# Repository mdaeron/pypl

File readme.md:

# Python Prep Line (PyPL)

An open source / open hardware automation system. Originally designed for processing geochemichal samples in our stable isotope lab, but the system is flexible enough to fit many other needs.

## Core design

* Microcontrollers are not encumbered by a full OS, yet can reliably run simple tasks with low latency (μs to ms).
* PyPL uses a *pyboard*, a microcontroller running MicroPython (a full-featured Python implementation running on “bare metal”) to communicate asynchronously with sensors
(T, P, H), and actuators (stepper motors, relays, valves, heating elements...).
* The board is also connected to a full-fledged computer (e.g., a Raspberry Pi or something more expensive) which provides a GUI and logs/syncs/backups data.
* PyPL mostly uses cheap (2–20 €) breakout boards for electronic components, making most repairs plug-and-play. These boards are cheap enough that you can have spare ones, further simplifying hardware maintenance.
* All code, whether on the pyboard or on the computer, is regular Python, promoting painless
development, rapid iteration, and future-proof code.

## Documentation

Full documentation (work in progress) is [here](https://mdaeron.github.io/pypl/).

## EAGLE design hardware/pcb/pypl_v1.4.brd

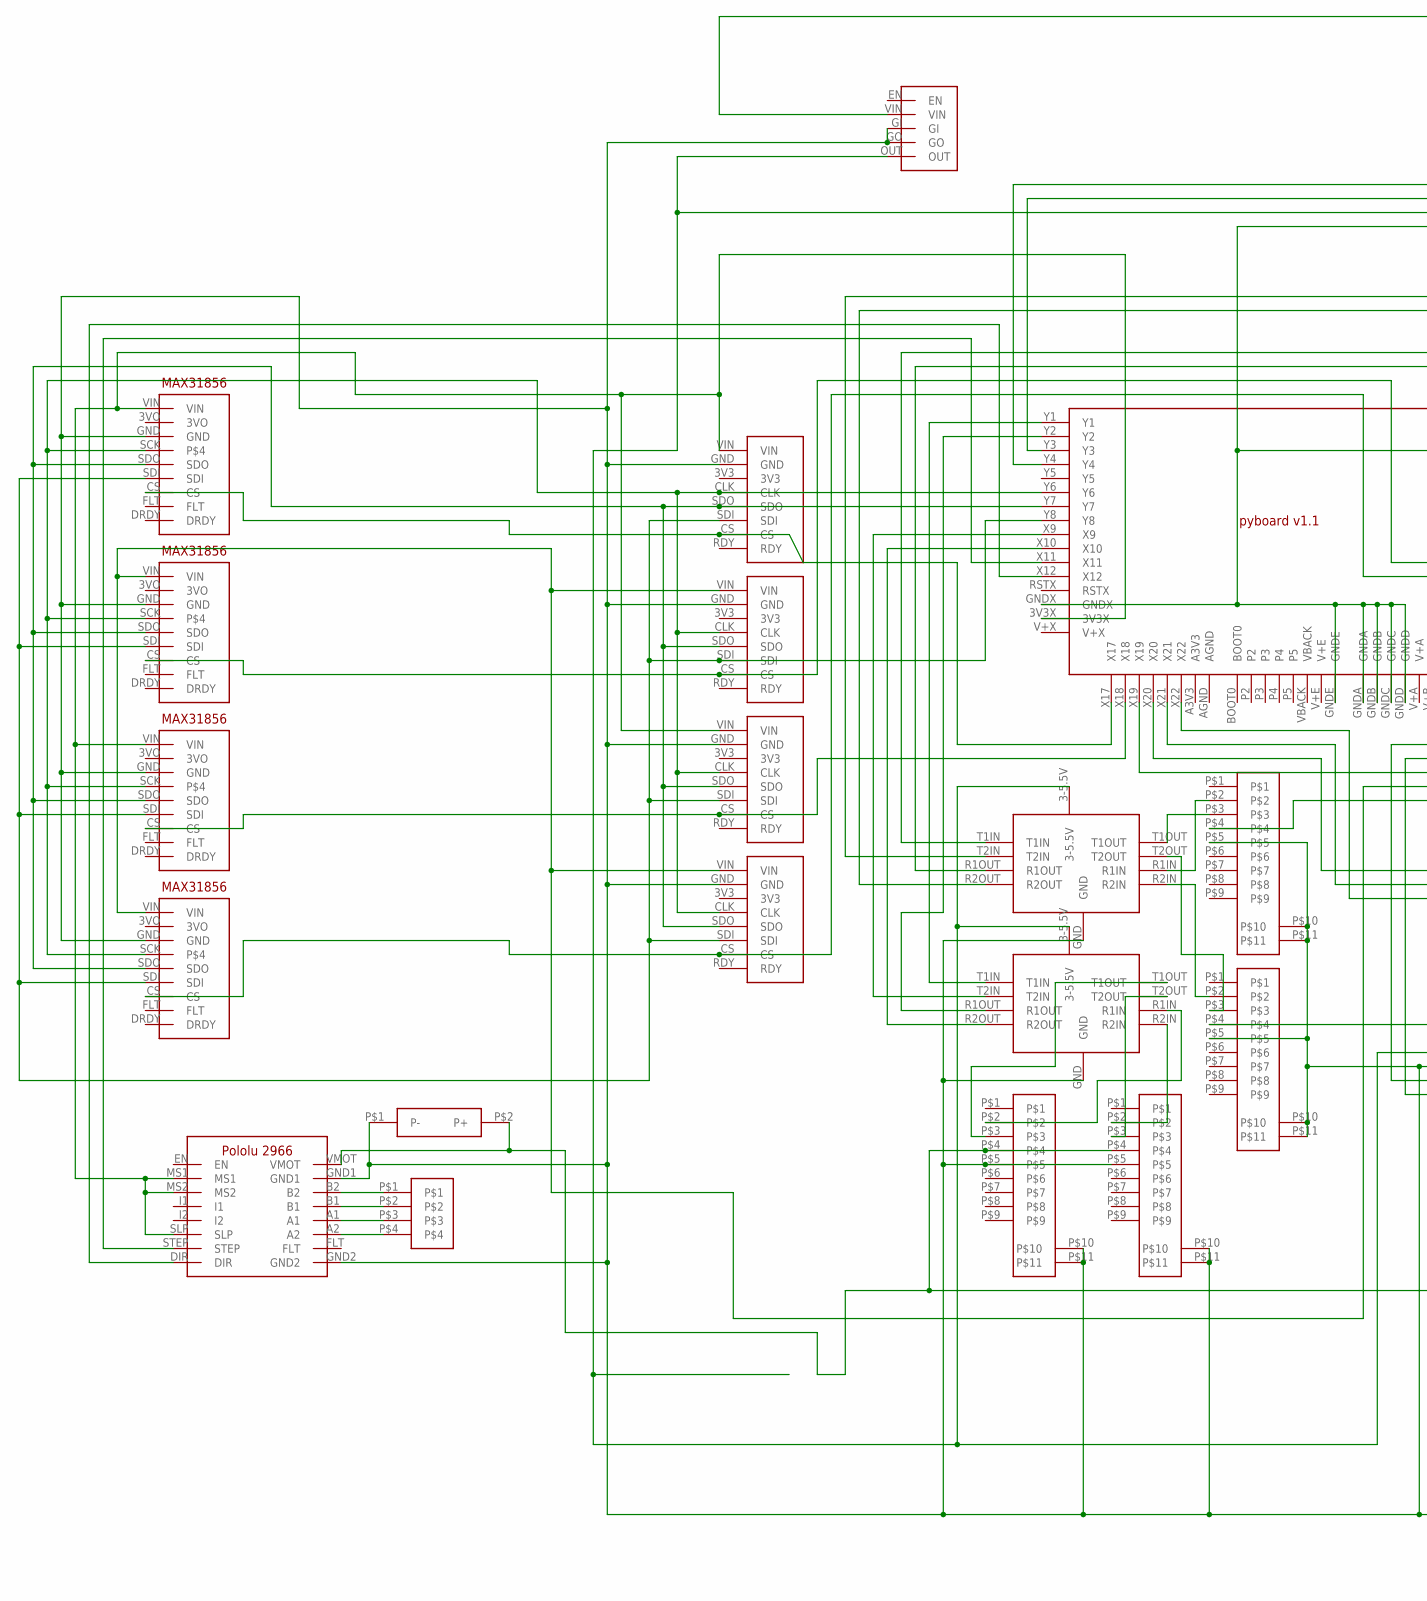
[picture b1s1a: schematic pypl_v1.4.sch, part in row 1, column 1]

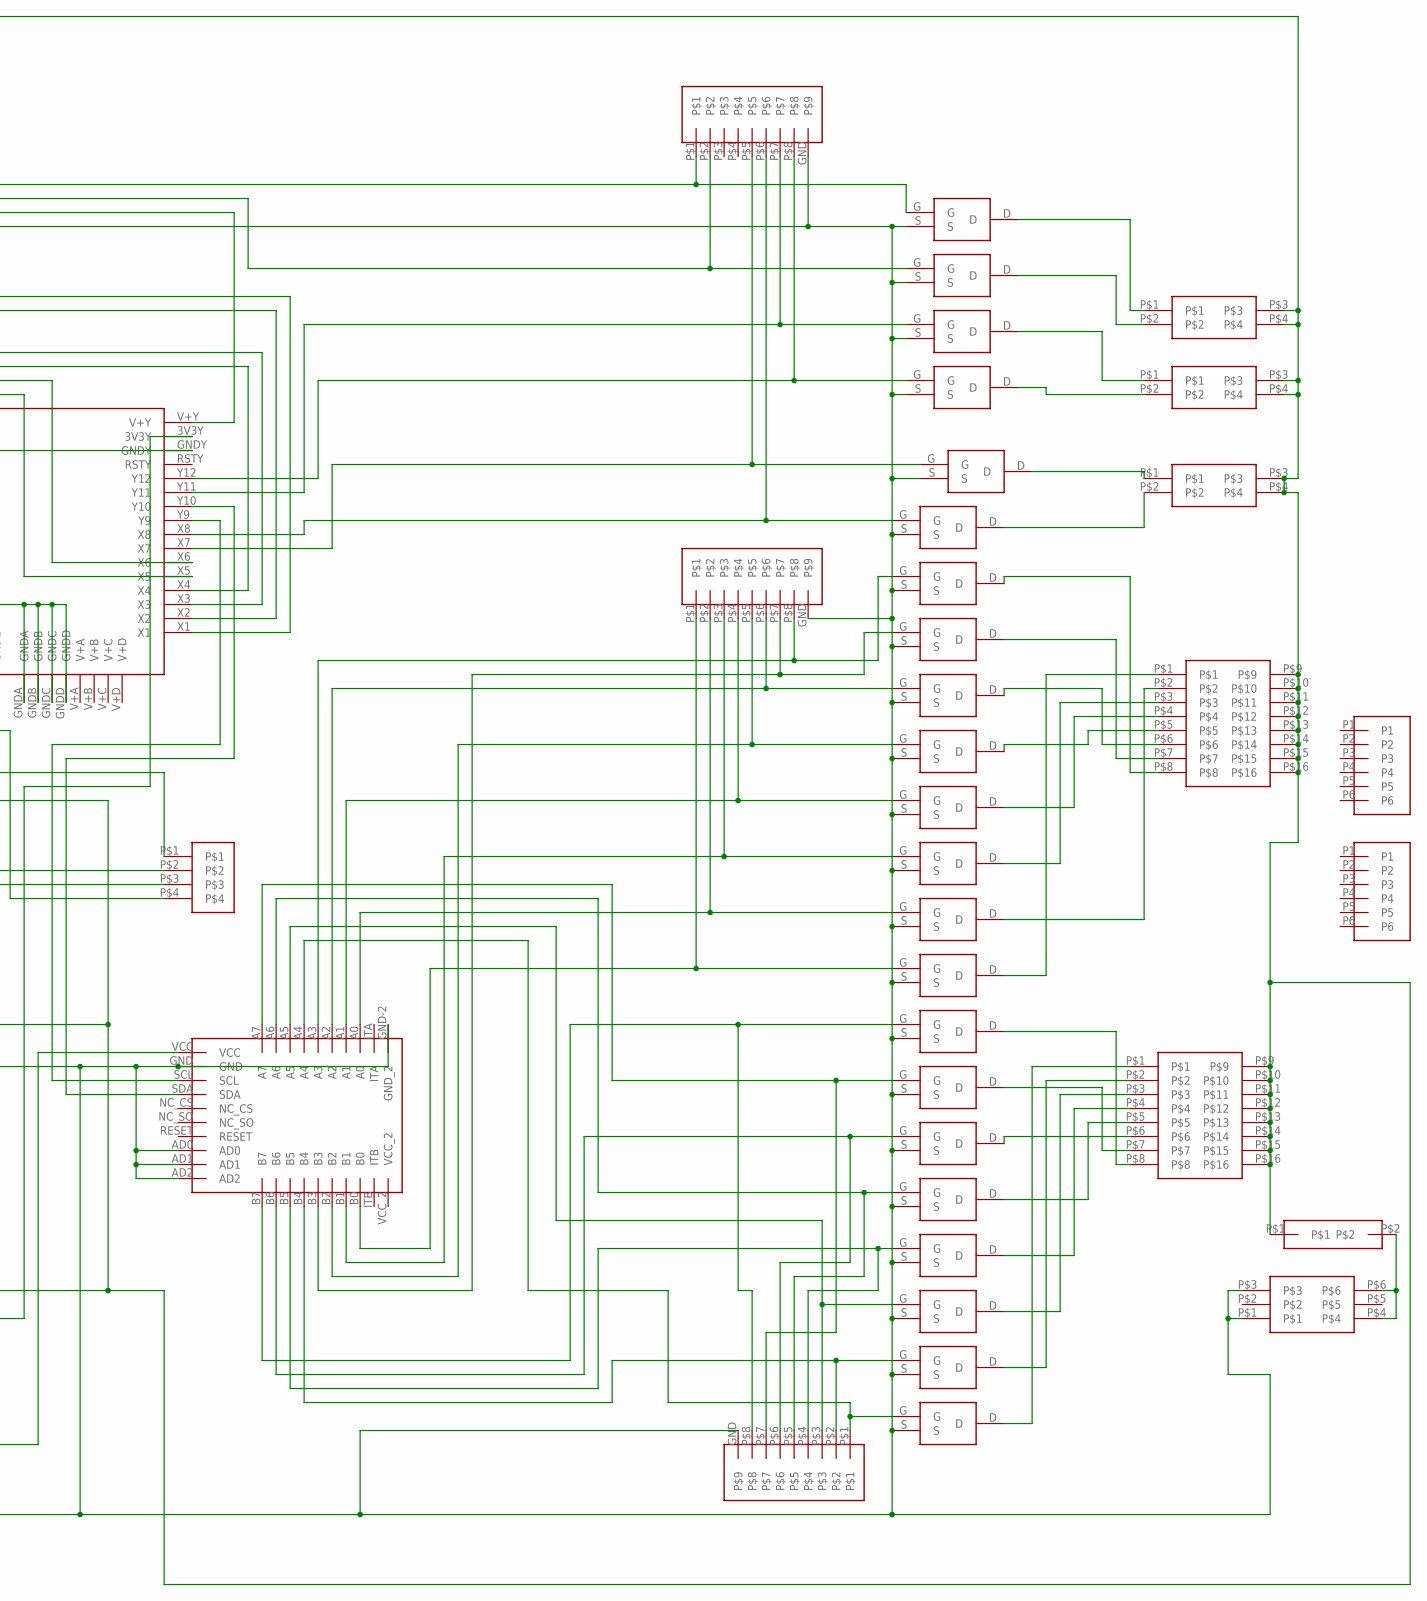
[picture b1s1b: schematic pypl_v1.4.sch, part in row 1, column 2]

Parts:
U$1, U$23, U$25, U$26: MAX31865
U$2, U$3, U$4, U$5, U$6, U$7, U$8, U$9, U$11, U$12, U$13, U$14, U$15, U$16, U$17, U$18, U$33, U$34, U$42, U$43, U$44, U$45: IRLB8721PBF
U$10: MCP23017
U$19, U$20, U$21, U$22: DSUB-9
U$24: PYBOARD_V1.1
U$27, U$28: BORNIER_DUPLEX_X16
U$29: CAP-GOTRONIC-04936
U$30, U$46: BORNIER_1X4_2.54
U$31: PORTE-FUSIBLE
U$32: MP6500-2966
U$35, U$40, U$41: BORNIER_DUPLEX_X4
U$36, U$37: BOB-1189; BOB-11189
U$38: MOLEX_MINIFT_JR_ANGLED_X6
U$39: D24V50F5D24V50F5; D24V50F5
U$47, U$48, U$49: RESISTOR_BANK_BUSSED_X8
U$50, U$51, U$52, U$53: MAX31856
U$54, U$55: PINH06

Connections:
GND: U$1.GND, U$2.S, U$3.S, U$4.S, U$5.S, U$6.S, U$7.S, U$8.S, U$9.S, U$10.AD0, U$10.AD1, U$10.AD2, U$10.GND, U$10.GND-2 (GND_2), U$11.S, U$12.S, U$13.S, U$14.S, U$15.S, U$16.S, U$17.S, U$18.S, U$19.P$5, U$19.P$10, U$19.P$11, U$20.P$5, U$20.P$10, U$20.P$11, U$21.P$5, U$21.P$10, U$21.P$11, U$22.P$5, U$22.P$10, U$22.P$11, U$23.GND, U$24.GNDA, U$24.GNDB, U$24.GNDC, U$24.GNDD, U$24.GNDE, U$24.GNDX, U$24.GNDY, U$25.GND, U$26.GND, U$29.P$1 (P-), U$32.GND1, U$32.GND2, U$33.S, U$34.S, U$36.GND, U$37.GND, U$38.P$1, U$38.P$3, U$39.GI, U$39.GO, U$42.S, U$43.S, U$44.S, U$45.S, U$47.GND, U$48.GND, U$49.GND, U$50.GND, U$51.GND, U$52.GND, U$53.GND
unnamed: U$24.X12, U$32.DIR
unnamed: U$10.SDA, U$24.Y10
unnamed: U$10.SCL, U$24.Y9
unnamed: U$24.X4, U$36.R1OUT
unnamed: U$24.X3, U$36.T1IN
unnamed: U$24.X2, U$36.R2OUT
unnamed: U$24.X1, U$36.T2IN
unnamed: U$24.Y1, U$37.T1IN
unnamed: U$24.Y2, U$37.R1OUT
unnamed: U$24.X10, U$37.R2OUT
unnamed: U$24.X9, U$37.T2IN
unnamed: U$1.CLK, U$23.CLK, U$24.Y6, U$25.CLK, U$26.CLK, U$50.SCK, U$51.SCK, U$52.SCK, U$53.SCK
unnamed: U$1.SDO, U$23.SDO, U$24.Y7, U$25.SDO, U$26.SDO, U$50.SDO, U$51.SDO, U$52.SDO, U$53.SDO
unnamed: U$1.SDI, U$23.SDI, U$24.Y8, U$25.SDI, U$26.SDI, U$50.SDI, U$51.SDI, U$52.SDI, U$53.SDI
unnamed: U$10.A7, U$15.G, U$47.P$7
unnamed: U$4.G, U$10.B2, U$48.P$5
unnamed: U$7.G, U$10.A3, U$48.P$8
unnamed: U$6.G, U$10.B3, U$48.P$7
unnamed: U$5.G, U$10.A2, U$48.P$6
unnamed: U$3.G, U$10.A1, U$48.P$4
unnamed: U$2.G, U$10.B1, U$48.P$3
unnamed: U$8.G, U$10.A0, U$48.P$2
unnamed: U$9.G, U$10.B0, U$48.P$1
unnamed: U$10.B4, U$17.G, U$47.P$2
unnamed: U$10.B5, U$12.G, U$47.P$4
unnamed: U$10.B6, U$14.G, U$47.P$6
unnamed: U$10.B7, U$16.G, U$47.P$8
unnamed: U$10.A6, U$13.G, U$47.P$5
unnamed: U$7.D, U$28.P$8
unnamed: U$6.D, U$28.P$7
unnamed: U$5.D, U$28.P$6
unnamed: U$30.P$1, U$32.B2
unnamed: U$16.D, U$27.P$8
unnamed: U$15.D, U$27.P$7
unnamed: U$4.D, U$28.P$5
unnamed: U$3.D, U$28.P$4
unnamed: U$2.D, U$28.P$3
unnamed: U$8.D, U$28.P$2
unnamed: U$9.D, U$28.P$1
unnamed: U$14.D, U$27.P$6
unnamed: U$13.D, U$27.P$5
unnamed: U$12.D, U$27.P$4
unnamed: U$11.D, U$27.P$3
unnamed: U$17.D, U$27.P$2
unnamed: U$18.D, U$27.P$1
unnamed: U$24.X19, U$46.P$1
unnamed: U$40.P$2, U$42.D
unnamed: U$10.VCC, U$24.V+Y, U$36.3-5.5V, U$37.3-5.5V, U$39.OUT
unnamed: U$31.P$2, U$38.P$4, U$38.P$6
unnamed: U$24.X6, U$26.CS, U$51.CS
unnamed: U$1.CS, U$24.X18, U$52.CS
unnamed: U$24.X17, U$25.CS, U$50.CS
unnamed: U$24.X7, U$34.G, U$49.P$5
unnamed: U$24.X8, U$33.G, U$49.P$6
unnamed: U$33.D, U$35.P$2
unnamed: U$34.D, U$35.P$1
unnamed: U$30.P$2, U$32.B1
unnamed: U$30.P$3, U$32.A1
unnamed: U$30.P$4, U$32.A2
unnamed: U$19.P$2, U$36.R1IN
unnamed: U$20.P$2, U$36.R2IN
unnamed: U$40.P$1, U$43.D
unnamed: U$21.P$2, U$37.R2IN
unnamed: U$22.P$2, U$37.R1IN
unnamed: U$19.P$3, U$36.T1OUT
unnamed: U$20.P$3, U$36.T2OUT
unnamed: U$22.P$3, U$37.T1OUT
unnamed: U$21.P$3, U$37.T2OUT
unnamed: U$1.VIN, U$24.3V3X, U$25.VIN, U$32.MS1, U$32.MS2, U$32.SLP, U$50.VIN, U$52.VIN
unnamed: U$23.CS, U$24.X5, U$53.CS
unnamed: U$41.P$2, U$44.D
unnamed: U$23.VIN, U$24.3V3Y, U$26.VIN, U$51.VIN, U$53.VIN
unnamed: U$19.P$4, U$20.P$4, U$21.P$4, U$22.P$4, U$27.P$9, U$27.P$10, U$27.P$11, U$27.P$12, U$27.P$13, U$27.P$14, U$27.P$15, U$27.P$16, U$28.P$9, U$28.P$10, U$28.P$11, U$28.P$12, U$28.P$13, U$28.P$14, U$28.P$15, U$28.P$16, U$29.P$2 (P+), U$31.P$1, U$32.VMOT, U$35.P$3, U$35.P$4, U$39.VIN, U$40.P$3, U$40.P$4, U$41.P$3, U$41.P$4
unnamed: U$24.X20, U$46.P$2
unnamed: U$24.X21, U$46.P$3
unnamed: U$24.X22, U$46.P$4
unnamed: U$24.X11, U$32.STEP
unnamed: U$10.A5, U$11.G, U$47.P$3
unnamed: U$41.P$1, U$45.D
unnamed: U$24.Y11, U$43.G, U$49.P$7
unnamed: U$24.Y12, U$42.G, U$49.P$8
unnamed: U$24.Y3, U$44.G, U$49.P$2
unnamed: U$24.Y4, U$45.G, U$49.P$1
unnamed: U$10.A4, U$18.G, U$47.P$1

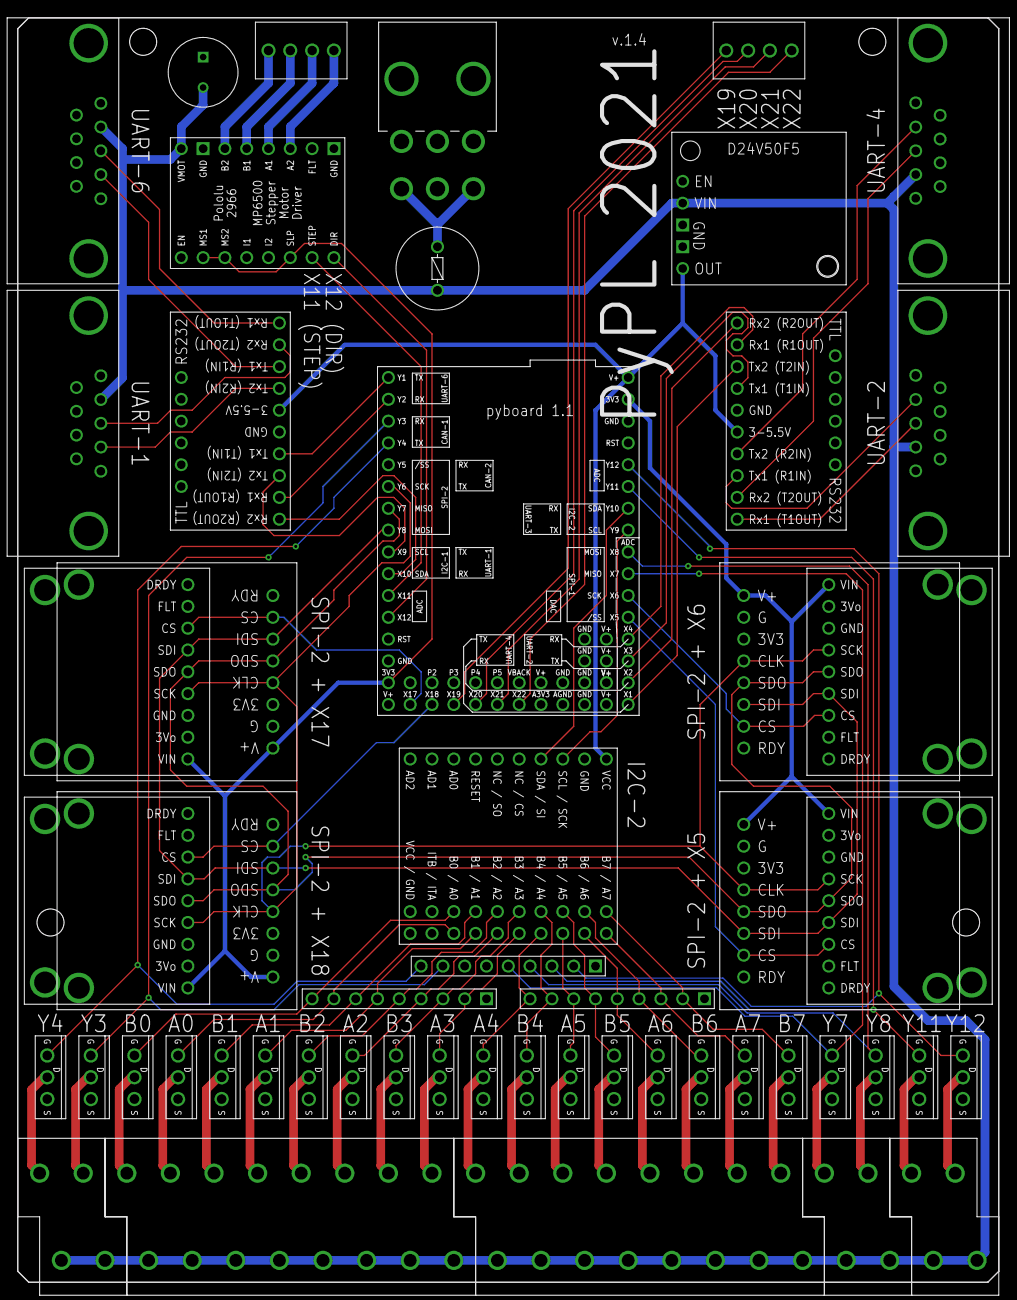
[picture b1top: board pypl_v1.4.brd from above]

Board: 2 copper layers, 114.3 x 147.3 mm, 55 parts (0 on the bottom side), 85 nets.

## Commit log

2020-12-13 Edit readme
2020-12-21 Add board code, 5V supply doc and pcb files
2020-12-22 Start work on gui
2020-12-22 Add Icon_Widget
2020-12-22 Add basic logging
2020-12-23 Add Dialog_Widget
2020-12-23 Add cancel dialogs
2020-12-23 Add rudimentary logging
2020-12-25 Add MAX31855 thermocouple board
2020-12-25 Add NIST correction to max31855.py
2020-12-25 Slightly accelerate NIST correction to max31855.py
2020-12-28 Add liveplot.py; further accelerate NIST correction to max31855.py
2020-12-28 Add RTC functionality
2020-12-28 Add PyPL_GUI.set_rtc()
2020-12-31 Read datetime objects in liveplot; corrected PyPL_GUI.set_rtc()
2020-12-31 Display notes in liveplot
2020-12-31 bugfix
2021-01-02 Improve logging
2021-01-03 Add temporary high-resolution logging
2021-01-03 Use defaultdict for gui state
2021-01-05 Add timing.py
2021-01-08 Add Stepper(), Heartbeat() and DummySensor()
2021-01-14 Better handling of missing sensors
2021-04-29 Many readme changes
2021-04-29 Fiddle with css.svg
2021-04-29 Remove css.svg
2021-04-29 Remove <style> in readme
2021-04-29 Add heading numbers in readme
2021-05-02 Add general schematic and update Eagle files
2021-05-02 Add general schematic
2021-05-02 Try centering image
2021-05-10 Add Max31856 and gui changes
2021-05-13 Define Thermostat(), extensive changes to gui.py and buid_gui_elements.py
2021-05-19 Use eval() to send instructions; add on-board error logging
2021-05-21 Stepper now uses interrupts rather than uasyncio
2021-05-22 Add method to relay commands directly to the board from terminal
2021-05-22 Add command buttons
2021-05-22 Add standby command to GUI
2021-05-22 Add confirm stop dialogs
2021-05-22 Add software/gui/img/command_carb.png
2021-05-23 Add acid pump and acid gauge
2021-05-23 Cosmetic GUI changes
2021-05-24 Add vacuum indicators to tubes in GUI
2021-05-24 Add more vacuum indicators
2022-02-06 changes to build_gui_elements.py
2023-08-30 Add windows port
2023-10-01 Add mkdocs
2023-10-01 First mkdocs deployment
2023-10-03 Improve docs
